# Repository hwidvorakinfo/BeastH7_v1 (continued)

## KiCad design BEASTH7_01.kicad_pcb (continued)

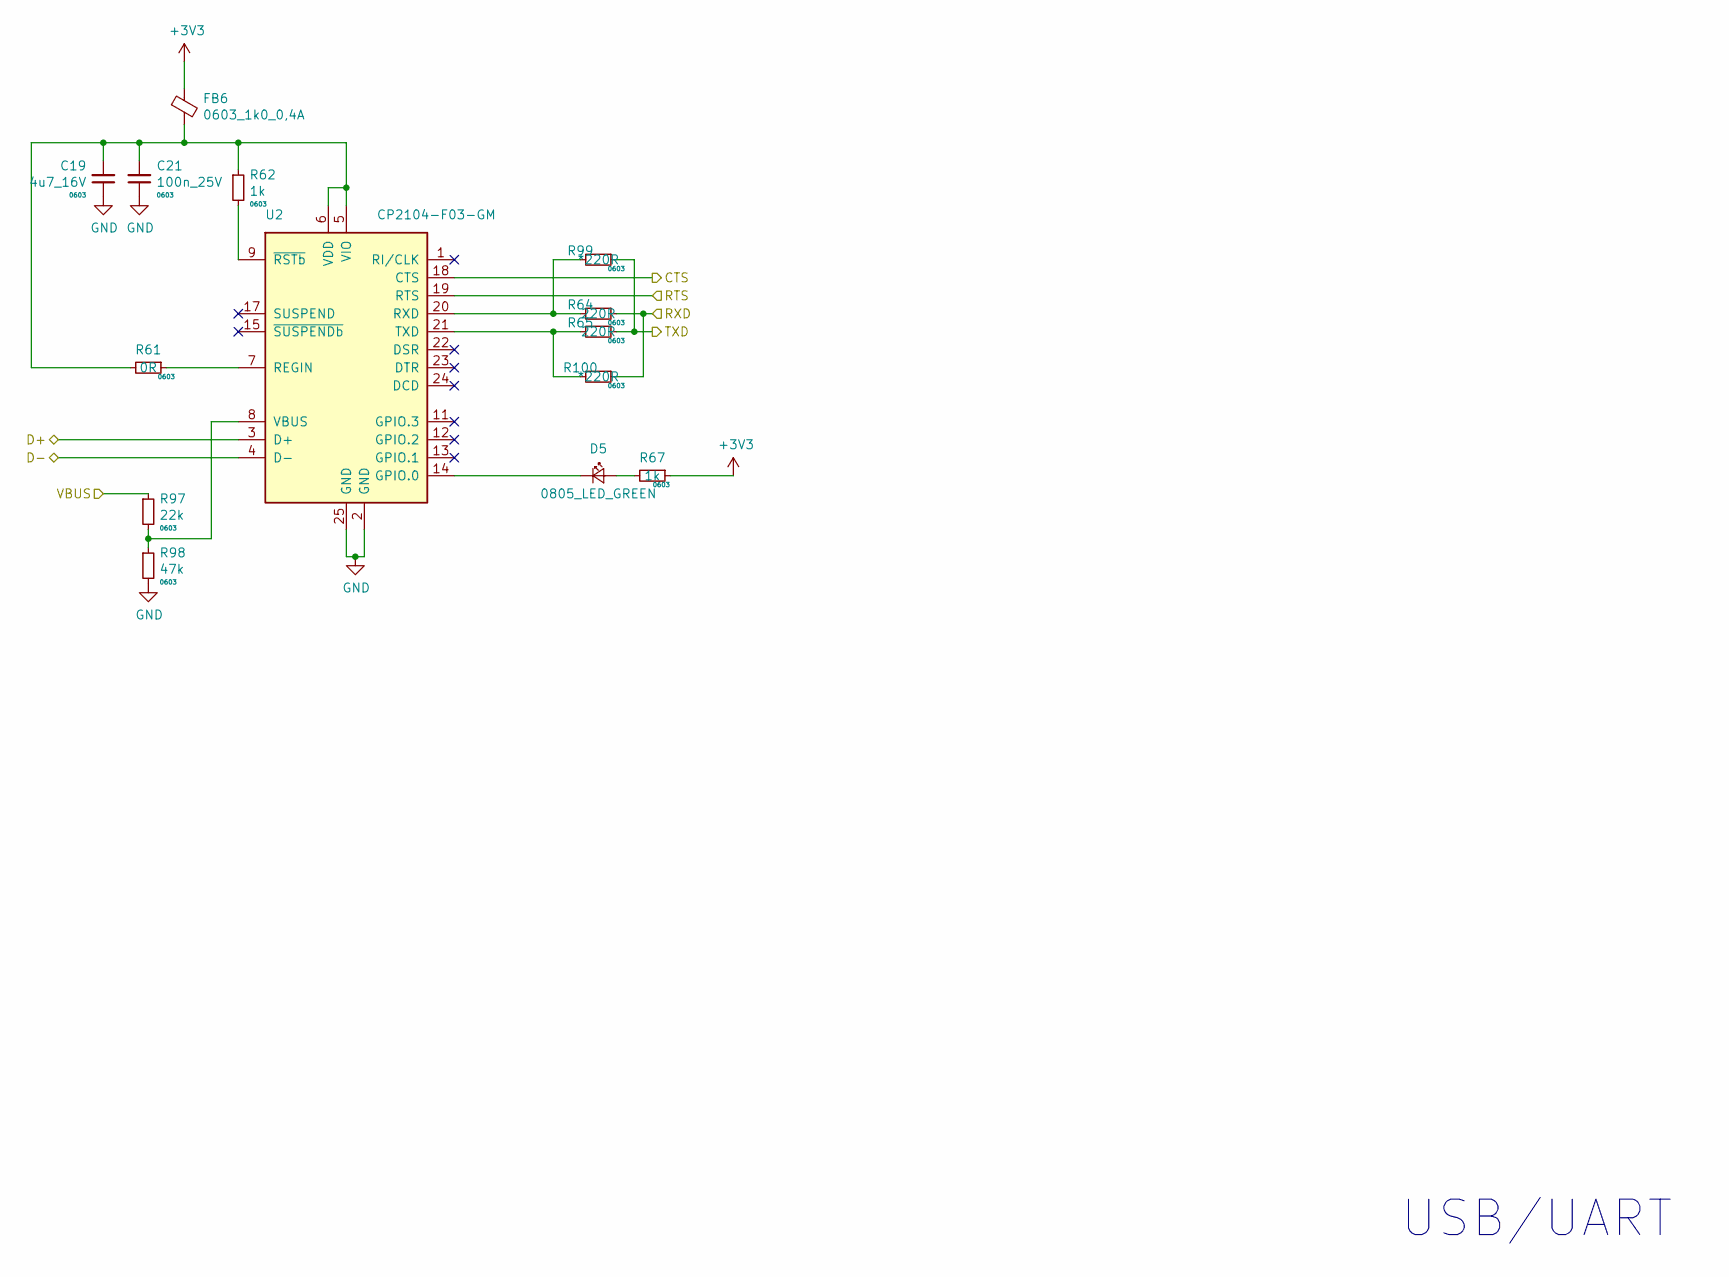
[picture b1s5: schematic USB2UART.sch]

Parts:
C19: 4u7_16V; C_0603_1608Metric
C21: 100n_25V; C_0603_1608Metric
D5: 0805_LED_GREEN; D_0805_2012Metric
FB6: 0603_1k0_0,4A; R_0603_1608Metric
R61: 0R; R_0603_1608Metric
R62, R67: 1k; R_0603_1608Metric
R64, R65: 220R; R_0603_1608Metric
R97: 22k; R_0603_1608Metric
R98: 47k; R_0603_1608Metric
R99, R100: *220R; R_0603_1608Metric
U2: CP2104-F03-GM; QFN-24-1EP_4x4mm_P0.5mm_EP2.6x2.6mm

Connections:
+3V3: FB6.1, R67.1; also elsewhere on the board
/USB-UART/CTS: U2.18 (CTS); also elsewhere on the board
/USB-UART/RTS: U2.19 (RTS); also elsewhere on the board
/USB-UART/RXD: R64.1, R100.1; also elsewhere on the board
/USB-UART/TXD: R65.1, R99.1; also elsewhere on the board
/USB_D+: U2.3 (D+); also elsewhere on the board
/USB_D-: U2.4 (D-); also elsewhere on the board
/VBUS: R97.1; also elsewhere on the board
GND: C19.1, C21.1, R98.2, U2.2 (GND), U2.25 (GND); also elsewhere on the board
unnamed: C19.2, C21.2, FB6.2, R61.2, R62.1, U2.5 (VIO), U2.6 (VDD)
unnamed: D5.1 (K), U2.14 (GPIO.0)
unnamed: D5.2 (A), R67.2
unnamed: R61.1, U2.7 (REGIN)
unnamed: R62.2, U2.9 (~RSTb)
unnamed: R64.2, R99.2, U2.20 (RXD)
unnamed: R97.2, R98.1, U2.8 (VBUS)
unnamed: R65.2, R100.2, U2.21 (TXD)

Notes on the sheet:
USB/UART

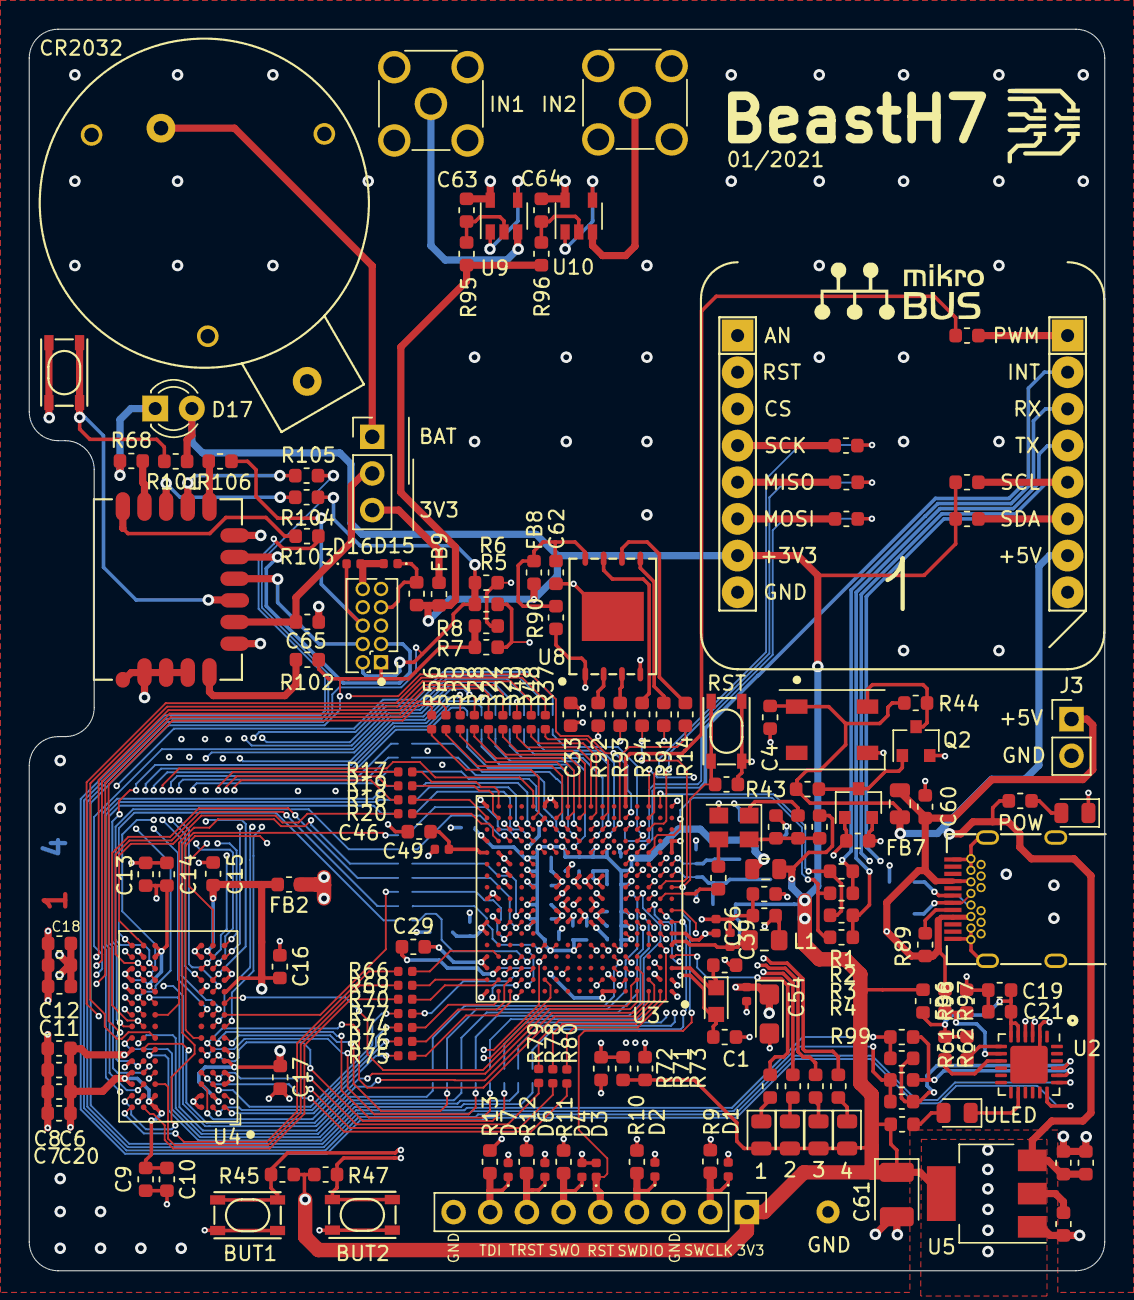
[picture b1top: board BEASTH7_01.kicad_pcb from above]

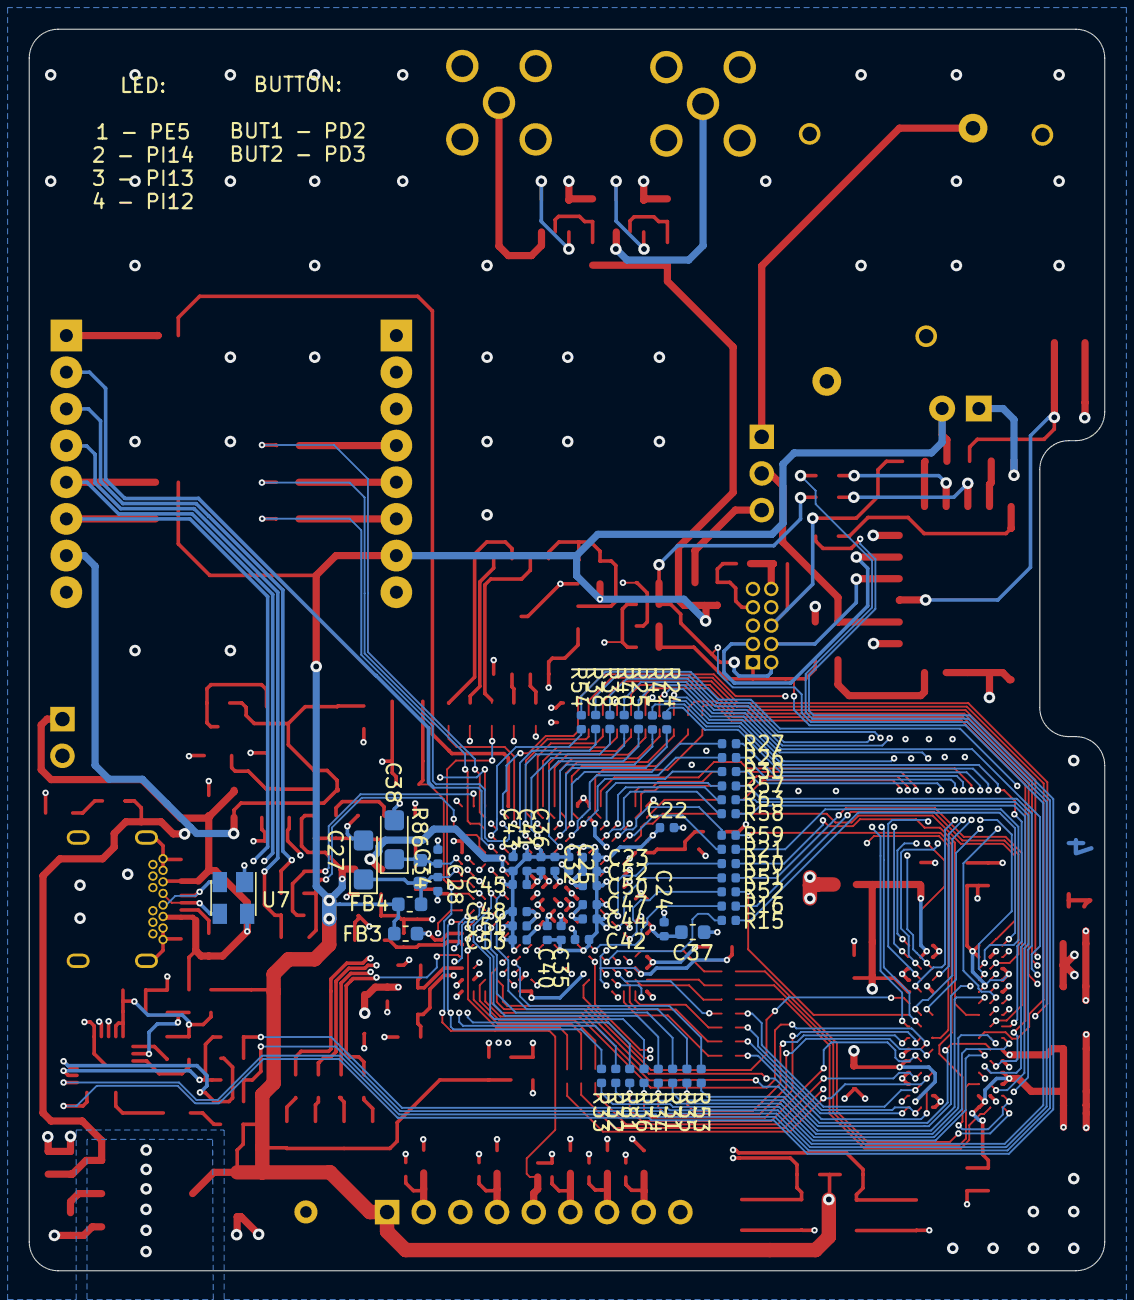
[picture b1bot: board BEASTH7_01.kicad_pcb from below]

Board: 4 copper layers, 74.5 x 86.0 mm, 230 parts (56 on the bottom side), 221 nets.

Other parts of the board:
BT1: CH25-2032LF
C62, C63, C64: 100n_25V; C_0603_1608Metric
C65: 100n_10V; C_0603_1608Metric
D15, D16: ESD9B5.0ST5G; D_0402_1005Metric
D17: 3MM_GREEN_LUG30243; LED_D3.0mm
FB8, FB9: 0603_1k0_0,4A; R_0603_1608Metric
J5, J6: SMA_angle; SMA_Molex_73251-2200_Horizontal
J7: S1G20_01x03; PinHeader_1x03_P2.54mm_Vertical
J9: 20021311-00010T4LF_2x5_1,27mm; PinHeader_2x05_P1.27mm_Vertical
R68, R106: 1k; R_0603_1608Metric
R90, R101: 10k; R_0603_1608Metric
R91, R92, R93, R94, R102, R103, R104, R105: 33R; R_0603_1608Metric
R95, R96: 10R; R_0603_1608Metric
R107: 0R; R_0603_1608Metric
S4: PTS810; MIKROSPINAC_PTS810
U1: LOGO_IDVORAK; logo_idvorak_silk_top_5mm
U8: MT25QL512_8PIN; W-PDFN-8_8x6MM
U9, U10: MCP6001R; SOT-23-5
U12: DA14531MOD

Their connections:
+3V3: D17.2, FB8.1, FB9.2, R95.1, R96.1, R101.1, R107.2; also elsewhere on the board
/ADC Vstupy/INPUT1: U9.1, U9.4; also elsewhere on the board
/ADC Vstupy/INPUT2: U10.1, U10.4; also elsewhere on the board
/Bluetooth/BT_BUTTON: R101.2, S4.3, S4.4, U12.8
/Bluetooth/BT_RST: D16.1, J9.6, R106.1; also elsewhere on the board
/Bluetooth/SWCLK: J9.3, U12.10
/Bluetooth/SWDIO: J9.4, U12.9
/MCU/QSPI_BK1_CLK: U8.6; also elsewhere on the board
/MCU/QSPI_BK1_IO0: R91.2; also elsewhere on the board
/MCU/QSPI_BK1_IO1: R92.2; also elsewhere on the board
/MCU/QSPI_BK1_IO2: R93.2; also elsewhere on the board
/MCU/QSPI_BK1_IO3: R94.2; also elsewhere on the board
/MCU/QSPI_BK1_NCS: R90.2, U8.1; also elsewhere on the board
/QSPI FLASH/QSPI_VDD: C62.1, FB8.2, R90.1, U8.8
/USB-UART/CTS: R103.1; also elsewhere on the board
/USB-UART/RTS: R105.1; also elsewhere on the board
/USB-UART/RXD: J9.2, R104.1; also elsewhere on the board
/USB-UART/TXD: J9.1, R102.2; also elsewhere on the board
GND: BT1.2, C62.2, C63.2, C64.2, C65.2, D15.2, D16.2, J5.2, J6.2, J9.8, J9.10, S4.1, S4.2, U8.4, U9.5, U10.5, U12.1, U12.2, U12.3, U12.4, U12.6, U12.11; also elsewhere on the board
unnamed: BT1.1, J7.1
unnamed: C63.1, R95.2, U9.2
unnamed: C64.1, R96.2, U10.2
unnamed: C65.1, J7.2, U12.7
unnamed: D15.1, J9.7, R107.1
unnamed: D17.1, R68.1
unnamed: FB9.1, J7.3
unnamed: J5.1, U9.3
unnamed: J6.1, U10.3
unnamed: R68.2, U12.15
unnamed: R91.1, U8.5
unnamed: R92.1, U8.2
unnamed: R93.1, U8.3
unnamed: R94.1, U8.7
unnamed: R102.1, U12.5
unnamed: R103.2, U12.16
unnamed: R104.2, U12.14
unnamed: R105.2, U12.13
unnamed: R106.2, U12.12

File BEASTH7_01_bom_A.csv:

Component,Description,Part,References,Value,Footprint,Quantity Per PCB,Datasheet,Supplier,MOC,Size
1,Single-cell battery holder CR2032,CH25-2032LF,BT1,CH25-2032LF,CH25-2032LF,1,http://www.farnell.com/datasheets/1505855.pdf,Farnell,CH25-2032LF,
2,0603 100n 25V,100n_10V,C3 C4 C5 C6 C7 C8 C9 C10 C11 C12 C13 C14 C15 C16 C17 C18 C20 C56 C58 C60 C62 C63 C64 C65,100n_10V,C_0603_1608Metric,24,~,Farnell,MC0603B104M250CT,0603
3,0603 100n 25V,100n_25V,C21,100n_25V,C_0603_1608Metric,1,~,Farnell,MC0603B104M250CT,0603
4,0402 100n 6V3,100n_6V3,C22 C23 C24 C25 C28 C31 C32 C34 C35 C36 C40 C41 C42 C43 C44 C45 C47 C48 C49 C50 C51 C52 C53,100n_6V3,C_0402_1005Metric,23,~,Farnell,MC0402B104K100CT,0402
5,0603 10u 10V,10u_10V,C30,10u_10V,C_0603_1608Metric,1,~,Farnell,LMK107BBJ106MALT,0603
6,10u 16V tantal,10u_16V_TANB,C61,10u_16V_TANB,CP_EIA-3528-21_Kemet-B,1,http://www.farnell.com/datasheets/2049092.pdf,Farnell,TR3B106K016C0500,TANB
7,0402 10u 6V3,10u_6V3,C26,10u_6V3,C_0402_1005Metric,1,~,Farnell,GRM155R60J106ME44D,0402
8,0603 1p5 50V,1p5_50V,C1 C2,1p5_50V,C_0603_1608Metric,2,~,Farnell,CC0603CRNPO9BN1R5,0603
9,0603 1u0 10V,1u0_10V,C37 C55,1u0_10V,C_0603_1608Metric,2,~,Farnell,CL10B105KP8NNNC,0603
10,4u7 10V tantal,1u0_10V_TANA,C27 C38,1u0_10V_TANA,CP_EIA-3216-18_Kemet-A,2,http://www.farnell.com/datasheets/2049092.pdf,Farnell,T491A105K010AT,TANA
11,0402 220p 10V,220p_10V,C39,220p_10V,C_0402_1005Metric,1,~,Farnell,885012005015,0402
12,0603 2u2 25V,2u2_25V,C46,2u2_25V,C_0603_1608Metric,1,~,Farnell,GRM188C71E225KE11D,0603
13,4u7 10V tantal,4u7_10V_TANA,C54,4u7_10V_TANA,CP_EIA-3216-18_Kemet-A,1,http://www.farnell.com/datasheets/2049092.pdf,Farnell,TAJA475K010RNJ,TANA
14,0603 4u7 16V,4u7_16V,C19,4u7_16V,C_0603_1608Metric,1,~,Farnell,CL10A475KO8NNNC,0603
15,0603 4u7 6V3,4u7_6V3,C29 C33,4u7_6V3,C_0603_1608Metric,2,~,Farnell,CL10A475KQ8NNNC,0603
16,LED green 0805,0805_LED_GREEN,D5 D9 D10 D11 D12 D13,0805_LED_GREEN,D_0805_2012Metric,6,~,Farnell,SML-M13MTT86,
17,"LED green 3mm THT, 7000-15000 mcd",3MM_GREEN_LUG30243,D17,3MM_GREEN_LUG30243,LED_D3.0mm,1,https://www.tme.eu/Document/b5501a7851206353c58b0dd24e69dcce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,TME,LUB30243,
18,"TVS, 12.5 V, SOD-923, 2 Pinů, 5 V, 300 mW, ESD9B Series",ESD9B5.0ST5G,D1 D2 D3 D4 D6 D7 D15 D16,ESD9B5.0ST5G,D_0402_1005Metric,8,~,Farnell,ESD9B5.0ST5G,
19,RGB LED with integrated controller,WS2812B,D8,WS2812B,WS2812B_PLCC4_5.0x5.0mm_P3.2mm,1,https://cdn-shop.adafruit.com/datasheets/WS2812B.pdf,TME,WS2812B-V5,
20,"Ferrite bead, 0603",0603_18R_7.5A,FB3,0603_18R_7.5A,R_0603_1608Metric,1,~,Farnell,FBMJ1608HM180NTR,
21,"Ferrite bead, 0603","0603_1k0_0,4A",FB1 FB2 FB4 FB6 FB8 FB9,"0603_1k0_0,4A",R_0603_1608Metric,6,~,Farnell,BLM18AG102SN1D,
22,"Ferrite bead, 0805",0805_120R_3A,FB5 FB7,0805_120R_3A,R_0805_2012Metric,2,~,Farnell,BLM21PG121SN1D,
23,"2x5_1,27mm","20021311-00010T4LF_2x5_1,27mm",J9,"20021311-00010T4LF_2x5_1,27mm",PinHeader_2x05_P1.27mm_Vertical,1,~,Farnell,"20021311-00010T4LF, DS1065-03-2X5S8BV",
24,S1G20 1x1 kulaty otvor,S1G20_01x01K,J2,S1G20_01x01K,S1G20_1x1_kulaty,1,~,,,
25,S1G20 1x2,S1G20_01x02,J3,S1G20_01x02,PinHeader_1x02_P2.54mm_Vertical,1,~,GME,S1G20,
26,S1G20 1x3,S1G20_01x03,J7,S1G20_01x03,PinHeader_1x03_P2.54mm_Vertical,1,~,GME,S1G20,
27,S1G20 1x9,S1G20_01x09,J1,S1G20_01x09,PinHeader_1x09_P2.54mm_Vertical,1,~,GME,S1G20,
28,SMA angle Molex 73251-2200,SMA_angle,J5 J6,SMA_angle,SMA_Molex_73251-2200_Horizontal,2, ~,Farnell,73251-2200,
29,USB Full-Featured Type-C Receptacle connector,USB_C_Receptacle_flat,J4,USB_C_Receptacle_flat,USB-C_632723100011_1MM,1,http://katalog.we-online.de/datasheet/632723100011.pdf,Farnell,632723100011,
30,"2u2 0806 0,138 Ohm",2u2_0806,L1,2u2_0806,R_0805_2012Metric_Pad1.15x1.40mm_HandSolder,1,~,Farnell,LQM2MPN2R2NG0L,0806
31,"N-MOSFET 60V, 0,2A",2N7002E,Q1 Q2,2N7002E,SOT-23,2,~,Farnell,2N7002E,
32,0603 0R,0R,R71,*0R,R_0603_1608Metric,1,~,Farnell,MCWR06X000 PTL,0603
33,0603 220R,220R,R1 R4 R5 R8 R99 R100,*220R,R_0603_1608Metric,6,~,Farnell,MCWR06X2200FTL,0603
34,0603 0R,0R,R61 R72 R86 R87 R107,0R,R_0603_1608Metric,5,~,Farnell,MCWR06X000 PTL,0603
35,0603 100k,100k,R42,100k,R_0603_1608Metric,1,~,Farnell,MCMR06X1003FTL,0603
36,0603 10R,10R,R95 R96,10R,R_0603_1608Metric,2,~,Farnell,MCMR06X10R0FTL,0603
37,0603 10k,10k,R43 R44 R45 R46 R47 R73 R90 R101,10k,R_0603_1608Metric,8,~,Farnell,MCMR06X1002FTL,0603
38,0603 1k0,1k,R62 R67 R68 R82 R83 R84 R85 R88 R106,1k,R_0603_1608Metric,9,~,Farnell,MCWR06X1001FT,0603
39,0603 220R,220R,R2 R3 R6 R7 R64 R65,220R,R_0603_1608Metric,6,~,Farnell,MCWR06X2200FTL,0603
40,0603 22R,22R,R9 R10 R11 R12 R13,22R,R_0603_1608Metric,5,~,Farnell,MCWR06X22R0FTL,0603
41,0603 22k,22k,R97,22k,R_0603_1608Metric,1,~,Farnell,MCMR06X2202FTL,0603
42,0603 33R,33R,R14 R91 R92 R93 R94 R102 R103 R104 R105 R108 R109 R110 R113,33R,R_0603_1608Metric,13,~,Farnell,MCWR06X33R0FTL,0603
43,0402 33R,33R,R15 R16 R17 R18 R19 R20 R21 R22 R23 R24 R25 R26 R27 R28 R29 R30 R31 R32 R33 R34 R35 R36 R37 R38 R39 R40 R41 R48 R49 R50 R51 R52 R53 R54 R55 R56 R57 R58 R59 R63 R66 R69 R70 R74 R75 R76 R77 R78 R79 R80 R81,33R,R_0402_1005Metric,51,~,Farnell,MCWR04X33R0FTL,0402
44,0603 3k3,3k3,R111 R112,3k3,R_0603_1608Metric,2,~,Farnell,MCWR06X3301FTL,0603
45,0603 47R,47R,R60,47R,R_0603_1608Metric,1,~,Farnell,MCWR06X47R0FTL,0603
46,0603 47k,47k,R98,47k,R_0603_1608Metric,1,~,Farnell,MCMR06X4702FTL,0603
47,0603 56k,56k,R89,56k,R_0603_1608Metric,1,~,Farnell,MCWR06X5602FTL,0603
48,PTS 810 Series Microminiature SMT Top ActuatedMicrominiature SMT Top Actuated,PTS810,S1 S2 S3 S4,PTS810,MIKROSPINAC_PTS810,4,http://www.farnell.com/datasheets/2789835.pdf,Farnell,PTS810SJM250SMT,
49,"USB to UART master bridge, QFN-24",CP2104-F03-GM,U2,CP2104-F03-GM,QFN-24-1EP_4x4mm_P0.5mm_EP2.6x2.6mm,1,http://www.farnell.com/datasheets/2674215.pdf,Farnell,CP2104-F03-GM,
50,SmartBond TINYTM Module,DA14531MOD,U12,DA14531MOD,DA14531MOD,1,https://www.dialog-semiconductor.com/sites/default/files/da1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,Farnell,DA14531MOD-00F01002,
51,"256Mb SYNCHRONOUS DRAM, TF-BGA 90",IS45S32800J,U4,IS45S32800J,BGA-90_8.0x13.0mm_Layout2x3x15_P0.8mm,1,http://www.issi.com/WW/pdf/42-45S32800J.pdf,Digikey,IS42S32800J-6BLI,
52,,LOGO_IDVORAK,U1,LOGO_IDVORAK,logo_idvorak_silk_top_5mm,1,,,,
53,"1 MHz, R2R, 1.8V to 6.0V, SOT-23-5",MCP6001R,U9 U10,MCP6001R,SOT-23-5,2,http://ww1.microchip.com/downloads/en/DeviceDoc/22141b.pdf,Farnell,MCP6001RT-I/OT,
54,"512Mb, 3V Multiple I/O Serial Flash Memory, T-BGA 24 5x5",MT25QL512_8PIN,U8,MT25QL512_8PIN,W-PDFN-8_8x6MM,1,https://media-www.micron.com/-/media/client/global/documents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,Digikey,MT25QL512ABB8E12-0SIT TR,
55,"1A LDO, Vin 18V, positive, 3.3V fixed output, SOT-223",NCP1117-3.3,U5,NCP1117-3.3,SOT-223-3_TabPin2,1,http://www.diodes.com/datasheets/AP1117.pdf,Farnell,NCP1117LPST33T3G,
56,Ultra low capacitance double rail-to-rail ESD protection diode,PESD2ETH-X,U7,PESD2ETH-X,SOT-143,1,https://4donline.ihs.com/images/VipMasterIC/IC/NEXP/NEXP-S-A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,Farnell,PESD2ETH-XR,
57,"STM32 Family STM32H7 Series Microcontrollers, TFBGA240+25",STM32H757XIH6,U3,STM32H757XIH6,TFBGA-265_14x14mm_Layout17x17_P0.8mm,1,https://www.st.com/resource/en/datasheet/stm32h757xi.pdf,Farnell,STM32H757XIH6,
58,mikroE mikroBUS interface,mikroBUS,U11,mikroBUS,mikroBUS,1,https://download.mikroe.com/documents/standards/mikrobus/mik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,,,
59,SMD 3225 (3.2mm × 2.5mm × 1mm) 25 MHz,MCSJK-3N-25.00-3.3-50-B,X1,MCSJK-3N-25.00-3.3-50-B,Oscillator_SMD_Abracon_ASE-4Pin_3.2x2.5mm,1,http://www.abracon.com/Oscillators/ASV.pdf,Farnell,MCSJK-3N-25.00-3.3-50-B,
60,Two pin crystal,ABS06-32.768KHZ-9-T,Y1,ABS06-32.768KHZ-9-T,Crystal_SMD_2012-2Pin_2.0x1.2mm_HandSoldering,1,~,Farnell,ABS06-32.768KHZ-9-T,





Component Groups:,60
Component Count:,230
Fitted Components:,230
Number of PCBs:,1
Total components:,230
Schematic Version:,A
Schematic Date:,2020-12-21
BoM Date:,"2021 January 04, Monday 07:19:22"
Schematic Source:,/Users/daymoon/Library/Mobile Documents/com~apple~CloudDocs/Data/Design/BeastH7/BEASTH7_01/BEASTH7_01.sch
KiCad Version:,Eeschema (5.1.5-0-10_14)

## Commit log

2021-05-04 MCUH7POWER bug description added
